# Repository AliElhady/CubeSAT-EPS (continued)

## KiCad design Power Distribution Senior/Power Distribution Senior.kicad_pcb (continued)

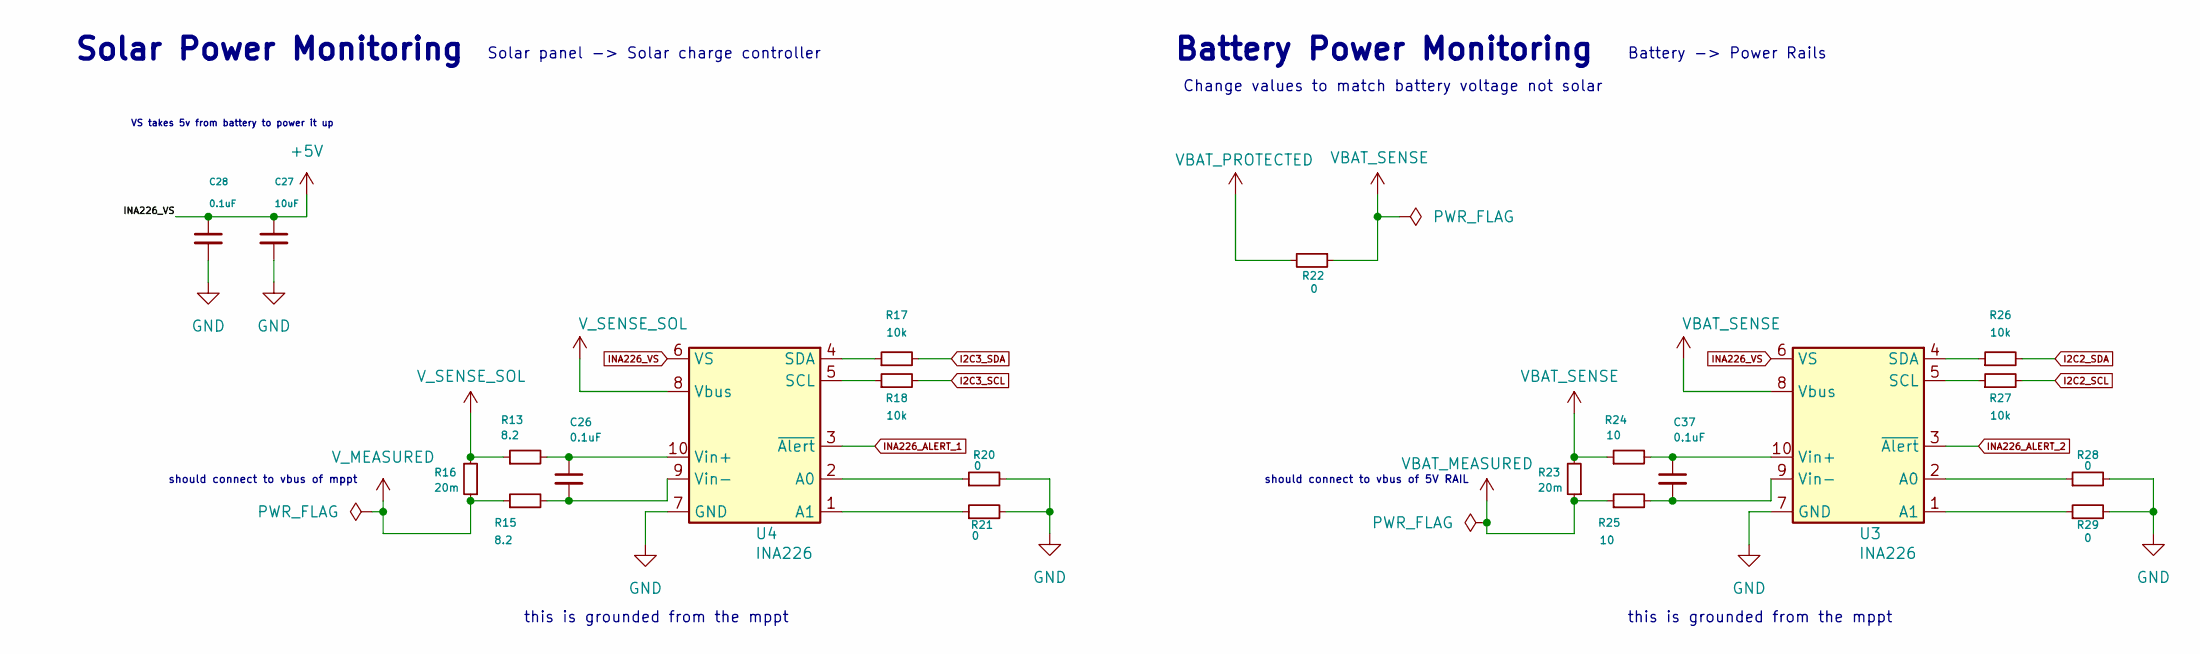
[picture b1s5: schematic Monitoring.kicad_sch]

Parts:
C26, C28, C37: 0.1uF; C_0603_1608Metric
C27: 10uF; C_0805_2012Metric
R13, R15: 8.2; R_0402_1005Metric
R16, R23: 20m; R_2512_6332Metric
R17, R18, R26, R27: 10k; R_0402_1005Metric
R20, R21, R22, R28, R29: 0; R_0805_2012Metric
R24, R25: 10; R_0603_1608Metric
U3, U4: INA226; VSSOP-10_3x3mm_P0.5mm

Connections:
GND: C27.2, C28.2, R20.2, R21.2, R28.2, R29.2, U3.7 (GND), U4.7 (GND); also elsewhere on the board
I2C2_SCL: R27.2; also elsewhere on the board
I2C2_SDA: R26.2; also elsewhere on the board
I2C3_SCL: R18.2; also elsewhere on the board
I2C3_SDA: R17.2; also elsewhere on the board
INA226_ALERT_1: U4.3 (~Alert); also elsewhere on the board
INA226_ALERT_2: U3.3 (~Alert); also elsewhere on the board
INA226_VS: C27.1, C28.1, U3.6 (VS), U4.6 (VS); also elsewhere on the board
unnamed: R28.1, U3.2 (A0)
unnamed: R29.1, U3.1 (A1)
unnamed: R27.1, U3.5 (SCL)
unnamed: R26.1, U3.4 (SDA)
unnamed: C37.1, R24.2, U3.10 (Vin+)
unnamed: C37.2, R25.2, U3.9 (Vin-)
unnamed: R20.1, U4.2 (A0)
unnamed: R21.1, U4.1 (A1)
unnamed: R18.1, U4.5 (SCL)
unnamed: R17.1, U4.4 (SDA)
unnamed: C26.1, R13.2, U4.10 (Vin+)
unnamed: C26.2, R15.2, U4.9 (Vin-)
VBAT_MEASURED: R23.1, R25.1; also elsewhere on the board
VBAT_PROTECTED: R22.2; also elsewhere on the board
VBAT_SENSE: R22.1, R23.2, R24.1, U3.8 (Vbus)
V_MEASURED: R15.1, R16.1; also elsewhere on the board
V_SENSE_SOL: R13.1, R16.2, U4.8 (Vbus); also elsewhere on the board

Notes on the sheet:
Solar panel -> Solar charge controller
Battery Power Monitoring
VS takes 5v from battery to power it up
this is grounded from the mppt
should connect to vbus of 5V RAIL
Battery -> Power Rails
Solar Power Monitoring
Change values to match battery voltage not solar
should connect to vbus of mppt

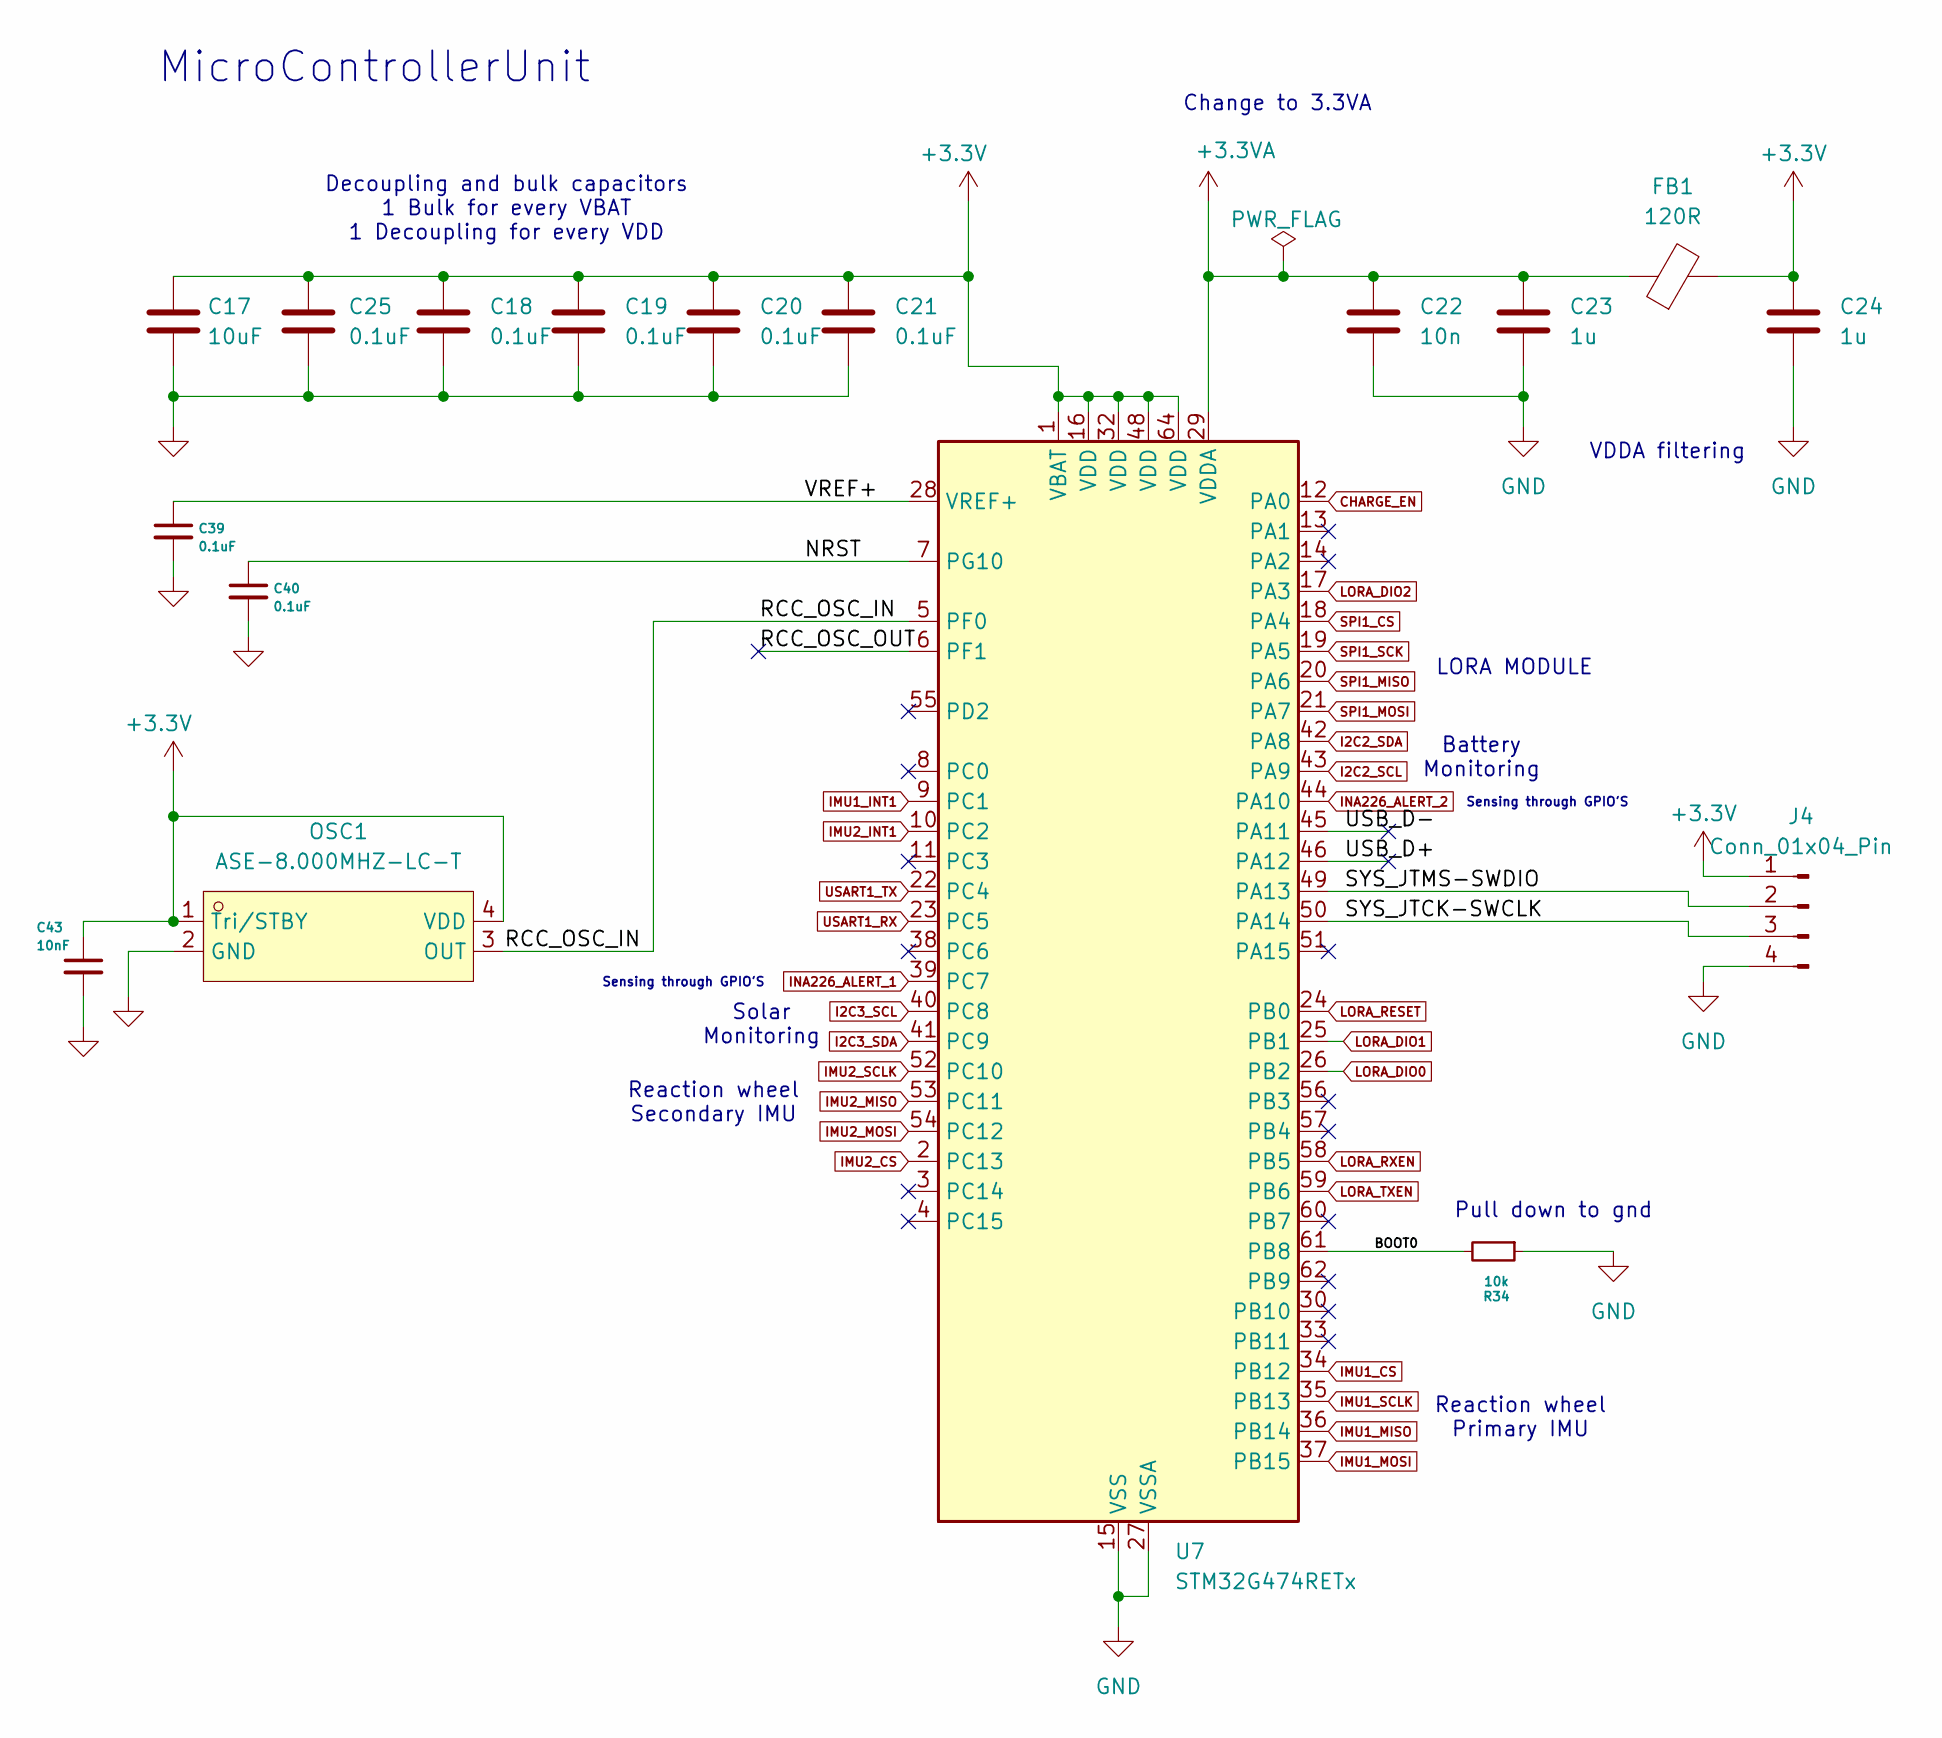
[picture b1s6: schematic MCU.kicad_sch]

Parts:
C17: 10uF; C_0805_2012Metric
C18, C19, C20, C21, C25: 0.1uF; C_0402_1005Metric
C22: 10n; C_0603_1608Metric
C23, C24: 1u; C_0603_1608Metric
C39, C40: 0.1uF; C_0603_1608Metric
C43: 10nF; C_0603_1608Metric
FB1: 120R; L_0603_1608Metric
J4: Conn_01x04_Pin; PinHeader_1x04_P2.54mm_Vertical
OSC1: ASE-8.000MHZ-LC-T; OSC-SMD_4P-L3.2-W2.5-CJ13-320001210A20; LCSC Part C6277872
R34: 10k; R_0402_1005Metric
U7: STM32G474RETx; LQFP-64_10x10mm_P0.5mm

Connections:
+3.3V: C17.1, C18.1, C19.1, C20.1, C21.1, C24.1, C25.1, C43.1, FB1.2, J4.1, OSC1.1 (Tri/STBY), OSC1.4 (VDD), U7.1 (VBAT), U7.16 (VDD), U7.32 (VDD), U7.48 (VDD), U7.64 (VDD); also elsewhere on the board
+3.3VA: C22.1, C23.1, FB1.1, U7.29 (VDDA)
/MCU/BOOT0: R34.2, U7.61 (PB8)
/MCU/NRST: C40.1, U7.7 (PG10)
/MCU/RCC_OSC_IN: OSC1.3 (OUT), U7.5 (PF0)
/MCU/RCC_OSC_OUT: U7.6 (PF1)
/MCU/SYS_JTCK-SWCLK: J4.3, U7.50 (PA14)
/MCU/SYS_JTMS-SWDIO: J4.2, U7.49 (PA13)
/MCU/USB_D+: U7.46 (PA12)
/MCU/USB_D-: U7.45 (PA11)
/MCU/VREF+: C39.1, U7.28 (VREF+)
CHARGE_EN: U7.12 (PA0); also elsewhere on the board
GND: C17.2, C18.2, C19.2, C20.2, C21.2, C22.2, C23.2, C24.2, C25.2, C39.2, C40.2, C43.2, J4.4, OSC1.2 (GND), R34.1, U7.15 (VSS), U7.27 (VSSA), U7.31 (VSS), U7.47 (VSS), U7.63 (VSS); also elsewhere on the board
I2C2_SCL: U7.43 (PA9); also elsewhere on the board
I2C2_SDA: U7.42 (PA8); also elsewhere on the board
I2C3_SCL: U7.40 (PC8); also elsewhere on the board
I2C3_SDA: U7.41 (PC9); also elsewhere on the board
IMU1_CS: U7.34 (PB12); also elsewhere on the board
IMU1_INT1: U7.9 (PC1); also elsewhere on the board
IMU1_MISO: U7.36 (PB14); also elsewhere on the board
IMU1_MOSI: U7.37 (PB15); also elsewhere on the board
IMU1_SCLK: U7.35 (PB13); also elsewhere on the board
IMU2_CS: U7.2 (PC13); also elsewhere on the board
IMU2_INT1: U7.10 (PC2); also elsewhere on the board
IMU2_MISO: U7.53 (PC11); also elsewhere on the board
IMU2_MOSI: U7.54 (PC12); also elsewhere on the board
IMU2_SCLK: U7.52 (PC10); also elsewhere on the board
INA226_ALERT_1: U7.39 (PC7); also elsewhere on the board
INA226_ALERT_2: U7.44 (PA10); also elsewhere on the board
LORA_DIO0: U7.26 (PB2); also elsewhere on the board
LORA_DIO1: U7.25 (PB1); also elsewhere on the board
LORA_DIO2: U7.17 (PA3); also elsewhere on the board
LORA_RESET: U7.24 (PB0); also elsewhere on the board
LORA_RXEN: U7.58 (PB5); also elsewhere on the board
LORA_TXEN: U7.59 (PB6); also elsewhere on the board
SPI1_CS: U7.18 (PA4); also elsewhere on the board
SPI1_MISO: U7.20 (PA6); also elsewhere on the board
SPI1_MOSI: U7.21 (PA7); also elsewhere on the board
SPI1_SCK: U7.19 (PA5); also elsewhere on the board
USART1_RX: U7.23 (PC5)
USART1_TX: U7.22 (PC4)

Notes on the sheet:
VDDA filtering
Pull down to gnd
Sensing through GPIO'S
Reaction wheel Primary IMU
LORA MODULE
MicroControllerUnit
Reaction wheel Secondary IMU
Battery Monitoring
Solar Monitoring
Change to 3.3VA
Decoupling and bulk capacitors 1 Bulk for every VBAT 1 Decoupling for every VDD

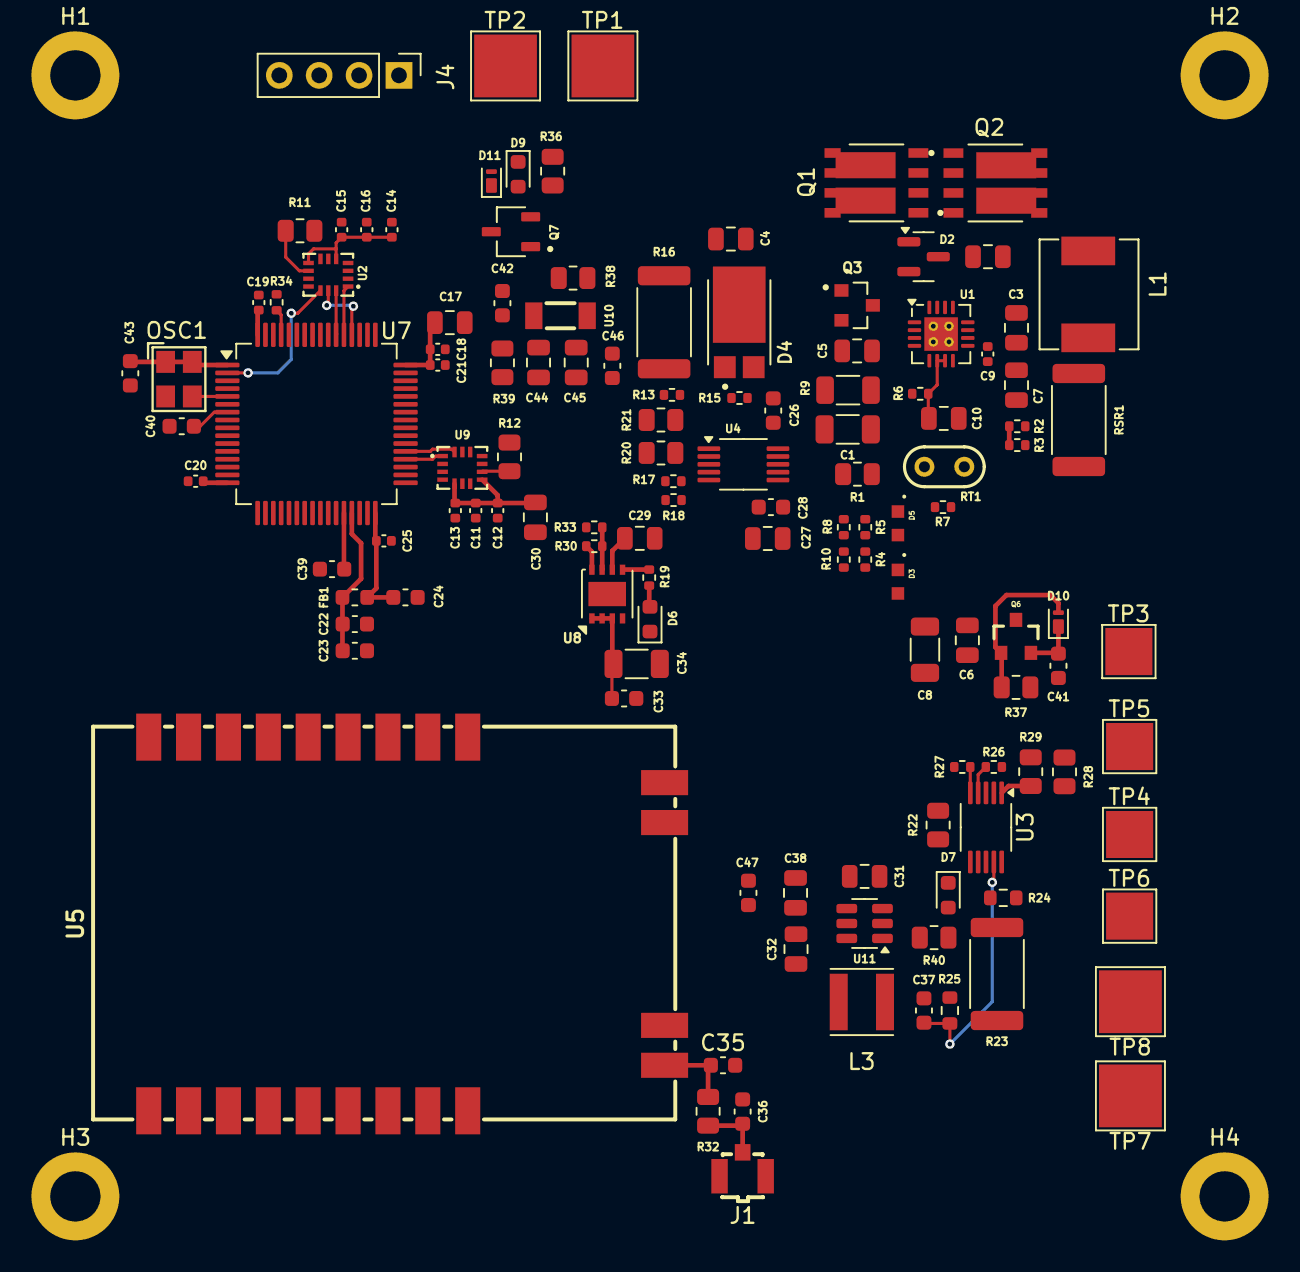
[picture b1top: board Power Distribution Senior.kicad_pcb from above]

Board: 4 copper layers, 128 parts (0 on the bottom side), 88 nets.

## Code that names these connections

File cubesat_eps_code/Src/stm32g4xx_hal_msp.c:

/* USER CODE BEGIN Header */
/**
  ******************************************************************************
  * @file         stm32g4xx_hal_msp.c
  * @brief        This file provides code for the MSP Initialization
  *               and de-Initialization codes.
  ******************************************************************************
  * @attention
  *
  * Copyright (c) 2026 STMicroelectronics.
  * All rights reserved.
  *
  * This software is licensed under terms that can be found in the LICENSE file
  * in the root directory of this software component.
  * If no LICENSE file comes with this software, it is provided AS-IS.
  *
  ******************************************************************************
  */
/* USER CODE END Header */

/* Includes ------------------------------------------------------------------*/
#include "main.h"
/* USER CODE BEGIN Includes */

/* USER CODE END Includes */

/* Private typedef -----------------------------------------------------------*/
/* USER CODE BEGIN TD */

/* USER CODE END TD */

/* Private define ------------------------------------------------------------*/
/* USER CODE BEGIN Define */

/* USER CODE END Define */

/* Private macro -------------------------------------------------------------*/
/* USER CODE BEGIN Macro */

/* USER CODE END Macro */

/* Private variables ---------------------------------------------------------*/
/* USER CODE BEGIN PV */

/* USER CODE END PV */

/* Private function prototypes -----------------------------------------------*/
/* USER CODE BEGIN PFP */

/* USER CODE END PFP */

/* External functions --------------------------------------------------------*/
/* USER CODE BEGIN ExternalFunctions */

/* USER CODE END ExternalFunctions */

/* USER CODE BEGIN 0 */

/* USER CODE END 0 */
/**
  * Initializes the Global MSP.
  */
void HAL_MspInit(void)
{

  /* USER CODE BEGIN MspInit 0 */

  /* USER CODE END MspInit 0 */

  __HAL_RCC_SYSCFG_CLK_ENABLE();
  __HAL_RCC_PWR_CLK_ENABLE();

  /* System interrupt init*/

  /** Disable the internal Pull-Up in Dead Battery pins of UCPD peripheral
  */
  HAL_PWREx_DisableUCPDDeadBattery();

  /* USER CODE BEGIN MspInit 1 */

  /* USER CODE END MspInit 1 */
}

/**
* @brief I2C MSP Initialization
* This function configures the hardware resources used in this example
* @param hi2c: I2C handle pointer
* @retval None
*/
void HAL_I2C_MspInit(I2C_HandleTypeDef* hi2c)
{
  GPIO_InitTypeDef GPIO_InitStruct = {0};
  RCC_PeriphCLKInitTypeDef PeriphClkInit = {0};
  if(hi2c->Instance==I2C2)
  {
  /* USER CODE BEGIN I2C2_MspInit 0 */

  /* USER CODE END I2C2_MspInit 0 */

  /** Initializes the peripherals clocks
  */
    PeriphClkInit.PeriphClockSelection = RCC_PERIPHCLK_I2C2;
    PeriphClkInit.I2c2ClockSelection = RCC_I2C2CLKSOURCE_PCLK1;
    if (HAL_RCCEx_PeriphCLKConfig(&PeriphClkInit) != HAL_OK)
    {
      Error_Handler();
    }

    __HAL_RCC_GPIOA_CLK_ENABLE();
    /**I2C2 GPIO Configuration
    PA8     ------> I2C2_SDA
    PA9     ------> I2C2_SCL
    */
    GPIO_InitStruct.Pin = GPIO_PIN_8|GPIO_PIN_9;
    GPIO_InitStruct.Mode = GPIO_MODE_AF_OD;
    GPIO_InitStruct.Pull = GPIO_PULLUP;
    GPIO_InitStruct.Speed = GPIO_SPEED_FREQ_LOW;
    GPIO_InitStruct.Alternate = GPIO_AF4_I2C2;
    HAL_GPIO_Init(GPIOA, &GPIO_InitStruct);

    /* Peripheral clock enable */
    __HAL_RCC_I2C2_CLK_ENABLE();
  /* USER CODE BEGIN I2C2_MspInit 1 */

  /* USER CODE END I2C2_MspInit 1 */
  }
  else if(hi2c->Instance==I2C3)
  {
  /* USER CODE BEGIN I2C3_MspInit 0 */

  /* USER CODE END I2C3_MspInit 0 */

  /** Initializes the peripherals clocks
  */
    PeriphClkInit.PeriphClockSelection = RCC_PERIPHCLK_I2C3;
    PeriphClkInit.I2c3ClockSelection = RCC_I2C3CLKSOURCE_PCLK1;
    if (HAL_RCCEx_PeriphCLKConfig(&PeriphClkInit) != HAL_OK)
    {
      Error_Handler();
    }

    __HAL_RCC_GPIOC_CLK_ENABLE();
    /**I2C3 GPIO Configuration
    PC8     ------> I2C3_SCL
    PC9     ------> I2C3_SDA
    */
    GPIO_InitStruct.Pin = GPIO_PIN_8|GPIO_PIN_9;
    GPIO_InitStruct.Mode = GPIO_MODE_AF_OD;
    GPIO_InitStruct.Pull = GPIO_PULLUP;
    GPIO_InitStruct.Speed = GPIO_SPEED_FREQ_LOW;
    GPIO_InitStruct.Alternate = GPIO_AF8_I2C3;
    HAL_GPIO_Init(GPIOC, &GPIO_InitStruct);

    /* Peripheral clock enable */
    __HAL_RCC_I2C3_CLK_ENABLE();
  /* USER CODE BEGIN I2C3_MspInit 1 */

  /* USER CODE END I2C3_MspInit 1 */
  }

}

/**
* @brief I2C MSP De-Initialization
* This function freeze the hardware resources used in this example
* @param hi2c: I2C handle pointer
* @retval None
*/
void HAL_I2C_MspDeInit(I2C_HandleTypeDef* hi2c)
{
  if(hi2c->Instance==I2C2)
  {
  /* USER CODE BEGIN I2C2_MspDeInit 0 */

  /* USER CODE END I2C2_MspDeInit 0 */
    /* Peripheral clock disable */
    __HAL_RCC_I2C2_CLK_DISABLE();

    /**I2C2 GPIO Configuration
    PA8     ------> I2C2_SDA
    PA9     ------> I2C2_SCL
    */
    HAL_GPIO_DeInit(GPIOA, GPIO_PIN_8);

    HAL_GPIO_DeInit(GPIOA, GPIO_PIN_9);

  /* USER CODE BEGIN I2C2_MspDeInit 1 */

  /* USER CODE END I2C2_MspDeInit 1 */
  }
  else if(hi2c->Instance==I2C3)
  {
  /* USER CODE BEGIN I2C3_MspDeInit 0 */

  /* USER CODE END I2C3_MspDeInit 0 */
    /* Peripheral clock disable */
    __HAL_RCC_I2C3_CLK_DISABLE();

    /**I2C3 GPIO Configuration
    PC8     ------> I2C3_SCL
    PC9     ------> I2C3_SDA
    */
    HAL_GPIO_DeInit(GPIOC, GPIO_PIN_8);

    HAL_GPIO_DeInit(GPIOC, GPIO_PIN_9);

  /* USER CODE BEGIN I2C3_MspDeInit 1 */

  /* USER CODE END I2C3_MspDeInit 1 */
  }

}

/**
* @brief SPI MSP Initialization
* This function configures the hardware resources used in this example
* @param hspi: SPI handle pointer
* @retval None
*/
void HAL_SPI_MspInit(SPI_HandleTypeDef* hspi)
{
  GPIO_InitTypeDef GPIO_InitStruct = {0};
  if(hspi->Instance==SPI1)
  {
  /* USER CODE BEGIN SPI1_MspInit 0 */

  /* USER CODE END SPI1_MspInit 0 */
    /* Peripheral clock enable */
    __HAL_RCC_SPI1_CLK_ENABLE();

    __HAL_RCC_GPIOA_CLK_ENABLE();
    /**SPI1 GPIO Configuration
    PA5     ------> SPI1_SCK
    PA6     ------> SPI1_MISO
    PA7     ------> SPI1_MOSI
    */
    GPIO_InitStruct.Pin = GPIO_PIN_5|GPIO_PIN_6|GPIO_PIN_7;
    GPIO_InitStruct.Mode = GPIO_MODE_AF_PP;
    GPIO_InitStruct.Pull = GPIO_PULLUP;
    GPIO_InitStruct.Speed = GPIO_SPEED_FREQ_LOW;
    GPIO_InitStruct.Alternate = GPIO_AF5_SPI1;
    HAL_GPIO_Init(GPIOA, &GPIO_InitStruct);

  /* USER CODE BEGIN SPI1_MspInit 1 */

  /* USER CODE END SPI1_MspInit 1 */
  }
  else if(hspi->Instance==SPI2)
  {
  /* USER CODE BEGIN SPI2_MspInit 0 */

  /* USER CODE END SPI2_MspInit 0 */
    /* Peripheral clock enable */
    __HAL_RCC_SPI2_CLK_ENABLE();

    __HAL_RCC_GPIOB_CLK_ENABLE();
    /**SPI2 GPIO Configuration
    PB13     ------> SPI2_SCK
    PB14     ------> SPI2_MISO
    PB15     ------> SPI2_MOSI
    */
    GPIO_InitStruct.Pin = GPIO_PIN_13|GPIO_PIN_14|GPIO_PIN_15;
    GPIO_InitStruct.Mode = GPIO_MODE_AF_PP;
    GPIO_InitStruct.Pull = GPIO_PULLUP;
    GPIO_InitStruct.Speed = GPIO_SPEED_FREQ_LOW;
    GPIO_InitStruct.Alternate = GPIO_AF5_SPI2;
    HAL_GPIO_Init(GPIOB, &GPIO_InitStruct);

  /* USER CODE BEGIN SPI2_MspInit 1 */

  /* USER CODE END SPI2_MspInit 1 */
  }

}

/**
* @brief SPI MSP De-Initialization
* This function freeze the hardware resources used in this example
* @param hspi: SPI handle pointer
* @retval None
*/
void HAL_SPI_MspDeInit(SPI_HandleTypeDef* hspi)
{
  if(hspi->Instance==SPI1)
  {
  /* USER CODE BEGIN SPI1_MspDeInit 0 */

  /* USER CODE END SPI1_MspDeInit 0 */
    /* Peripheral clock disable */
    __HAL_RCC_SPI1_CLK_DISABLE();

    /**SPI1 GPIO Configuration
    PA5     ------> SPI1_SCK
    PA6     ------> SPI1_MISO
    PA7     ------> SPI1_MOSI
    */
    HAL_GPIO_DeInit(GPIOA, GPIO_PIN_5|GPIO_PIN_6|GPIO_PIN_7);

  /* USER CODE BEGIN SPI1_MspDeInit 1 */

  /* USER CODE END SPI1_MspDeInit 1 */
  }
  else if(hspi->Instance==SPI2)
  {
  /* USER CODE BEGIN SPI2_MspDeInit 0 */

  /* USER CODE END SPI2_MspDeInit 0 */
    /* Peripheral clock disable */
    __HAL_RCC_SPI2_CLK_DISABLE();

    /**SPI2 GPIO Configuration
    PB13     ------> SPI2_SCK
    PB14     ------> SPI2_MISO
    PB15     ------> SPI2_MOSI
    */
    HAL_GPIO_DeInit(GPIOB, GPIO_PIN_13|GPIO_PIN_14|GPIO_PIN_15);

  /* USER CODE BEGIN SPI2_MspDeInit 1 */

  /* USER CODE END SPI2_MspDeInit 1 */
  }

}

/* USER CODE BEGIN 1 */

/* USER CODE END 1 */

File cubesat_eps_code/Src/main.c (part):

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  MX_SPI1_Init();
  /* USER CODE BEGIN 2 */
  HAL_GPIO_WritePin(GPIOA, GPIO_PIN_4,  GPIO_PIN_SET);  /* LORA_CS  */
  HAL_GPIO_WritePin(GPIOB, GPIO_PIN_12, GPIO_PIN_SET);  /* IMU1_CS  */
  HAL_GPIO_WritePin(GPIOC, GPIO_PIN_13, GPIO_PIN_SET);  /* IMU2_CS  */
  HAL_GPIO_WritePin(GPIOA, GPIO_PIN_12, GPIO_PIN_SET);  /* CHARGE_EN */

  HAL_GPIO_WritePin(GPIOB, GPIO_PIN_6, GPIO_PIN_RESET);   /* TXEN HIGH */
  HAL_GPIO_WritePin(GPIOB, GPIO_PIN_5, GPIO_PIN_RESET);
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  HAL_GPIO_WritePin(GPIOB, GPIO_PIN_0|GPIO_PIN_12|GPIO_PIN_5
                          |GPIO_PIN_6, GPIO_PIN_RESET);

  /*Configure GPIO pin : PC13 */
  GPIO_InitStruct.Pin = GPIO_PIN_13;
  GPIO_InitStruct.Mode = GPIO_MODE_OUTPUT_PP;
  GPIO_InitStruct.Pull = GPIO_NOPULL;
  GPIO_InitStruct.Speed = GPIO_SPEED_FREQ_LOW;
  HAL_GPIO_Init(GPIOC, &GPIO_InitStruct);

  /*Configure GPIO pins : PA4 PA12 */
  GPIO_InitStruct.Pin = GPIO_PIN_4|GPIO_PIN_12;
  GPIO_InitStruct.Mode = GPIO_MODE_OUTPUT_PP;
  GPIO_InitStruct.Pull = GPIO_NOPULL;
  GPIO_InitStruct.Speed = GPIO_SPEED_FREQ_LOW;
  HAL_GPIO_Init(GPIOA, &GPIO_InitStruct);

  /*Configure GPIO pins : PB0 PB2 PB12 PB5
                           PB6 */
  GPIO_InitStruct.Pin = GPIO_PIN_0|GPIO_PIN_12|GPIO_PIN_5
                          |GPIO_PIN_6;
  GPIO_InitStruct.Mode = GPIO_MODE_OUTPUT_PP;
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
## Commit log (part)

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2025-12-12 This commit Adds the Hardware folder
2025-12-16 Added FootPrints
2026-04-01 Updated pcb
2026-06-06 Add latest update to the file
2026-06-11 main.c
